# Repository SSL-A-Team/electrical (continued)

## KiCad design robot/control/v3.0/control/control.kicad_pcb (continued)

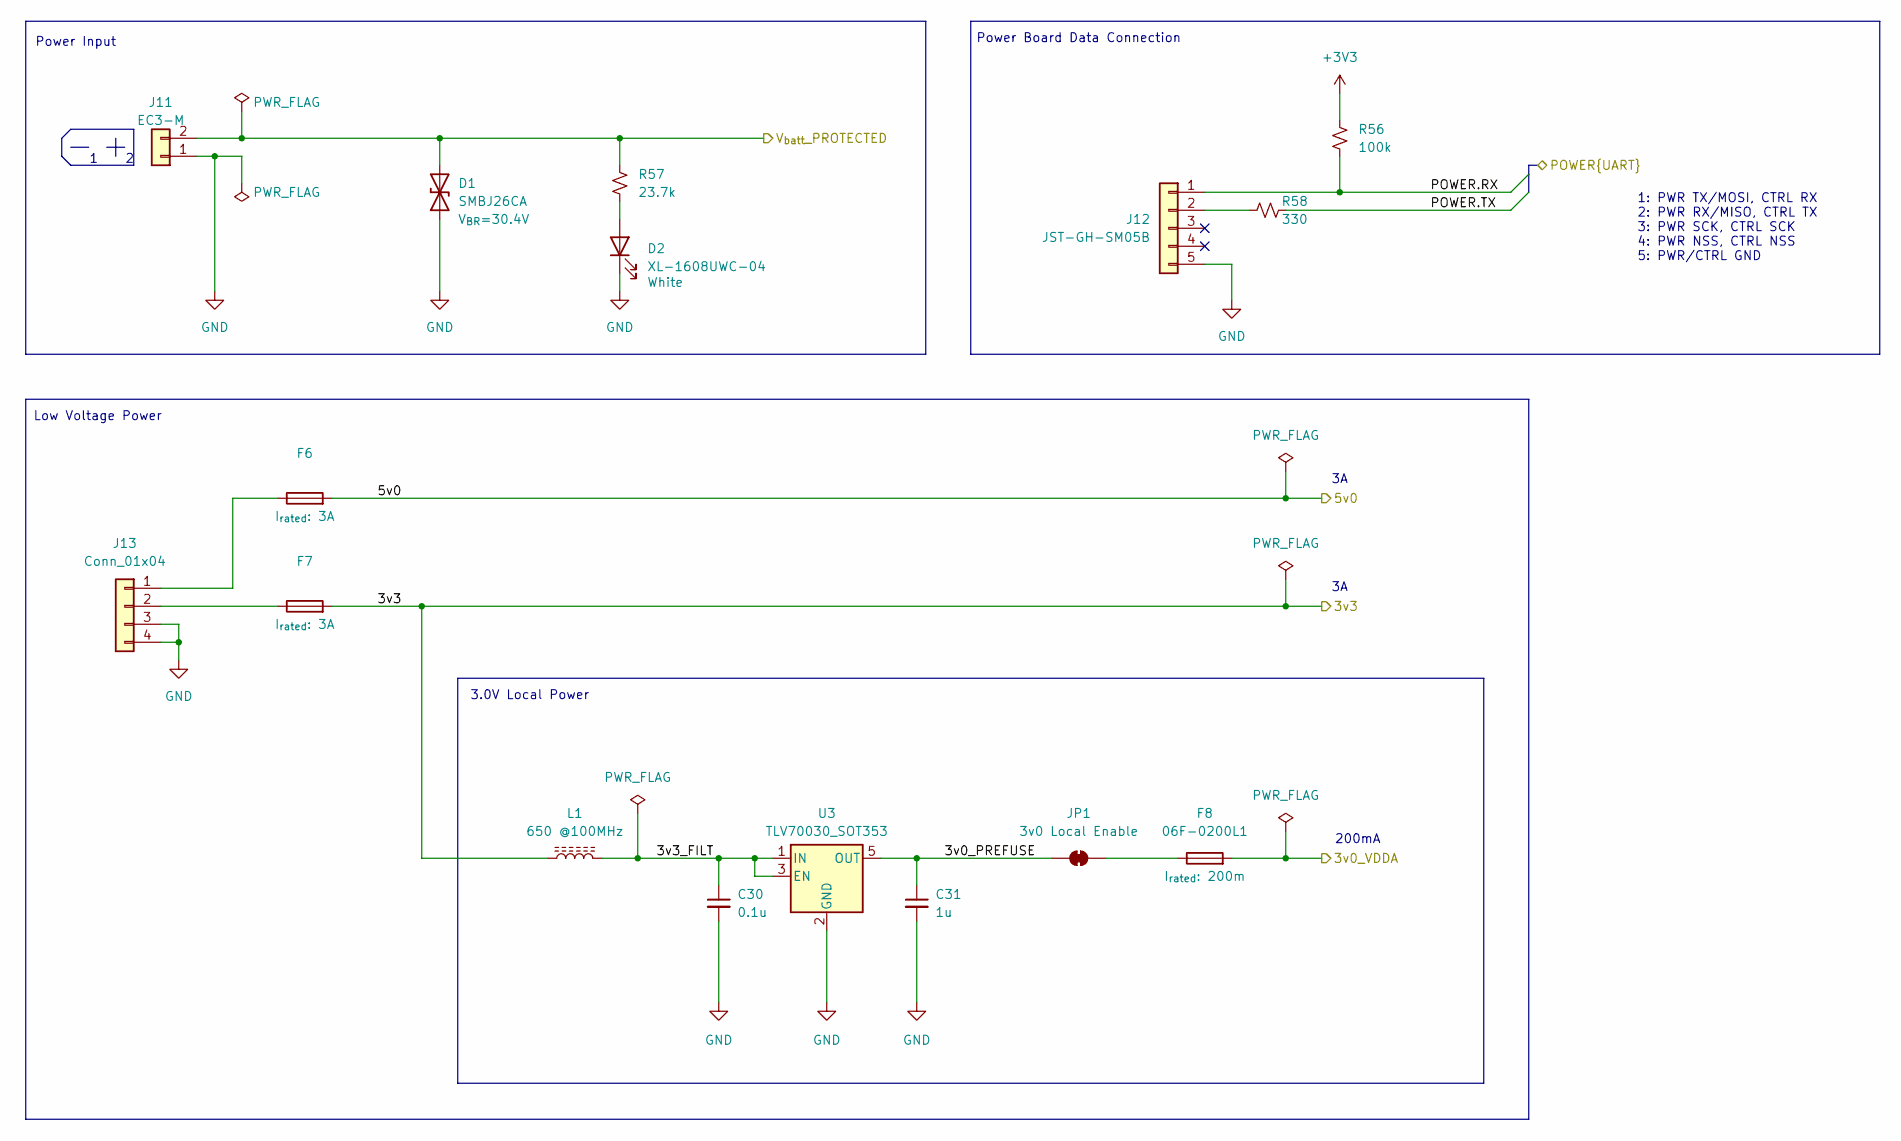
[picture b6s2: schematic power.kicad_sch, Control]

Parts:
C30: 0.1u; C_0402_1005Metric
C31: 1u; C_1206_3216Metric
D1: SMBJ26CA; D_SMB_Non-Polar
D2: XL-1608UWC-04; LED0603
F6, F7: Fuse_0603_1608Metric_Pad1.05x0.95mm_HandSolder
F8: 06F-0200L1; Fuse_0603_1608Metric_Pad1.05x0.95mm_HandSolder
J11: EC3-M; AMASS_XT30U-M_1x02_P5.0mm_Vertical
J12: JST-GH-SM05B; JST_GH_SM05B-GHS-TB_1x05-1MP_P1.25mm_Horizontal
J13: Conn_01x04; JST_PA_SM04B-PASS_1x04_P2.00mm_Horizontal
JP1: 3v0 Local Enable; SolderJumper-2_2.0x1.2mm_Closed
L1: 650 @100MHz; R_0603_1608Metric
R56: 100k; R_0402_1005Metric
R57: 23.7k; R_0402_1005Metric
R58: 330; R_0402_1005Metric
U3: TLV70030_SOT353; SOT-353_SC-70-5

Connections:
+3V0: F8.2; also elsewhere on the board
+3V3: F7.2, L1.1, R56.1; also elsewhere on the board
+5V: F6.2; also elsewhere on the board
+BATT: D1.2 (A2), J11.2, R57.1; also elsewhere on the board
/mcu/POWER.RX: J12.1, R56.2; also elsewhere on the board
/mcu/POWER.TX: R58.2; also elsewhere on the board
/power/3v0_PREFUSE: C31.1, JP1.1 (A), U3.5 (OUT)
/power/3v3_FILT: C30.1, L1.2, U3.1 (IN), U3.3 (EN)
GND: C30.2, C31.2, D1.1 (A1), D2.1 (K), J11.1, J12.5, J13.3, J13.4, U3.2 (GND); also elsewhere on the board
unnamed: D2.2 (A), R57.2
unnamed: J12.2, R58.1
unnamed: F6.1, J13.1
unnamed: F7.1, J13.2
unnamed: F8.1, JP1.2 (B)

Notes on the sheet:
200mA
Power Board Data Connection
1: PWR TX/MOSI, CTRL RX 2: PWR RX/MISO, CTRL TX 3: PWR SCK, CTRL SCK 4: PWR NSS, CTRL NSS 5: PWR/CTRL GND
Low Voltage Power
Power Input
3.0V Local Power

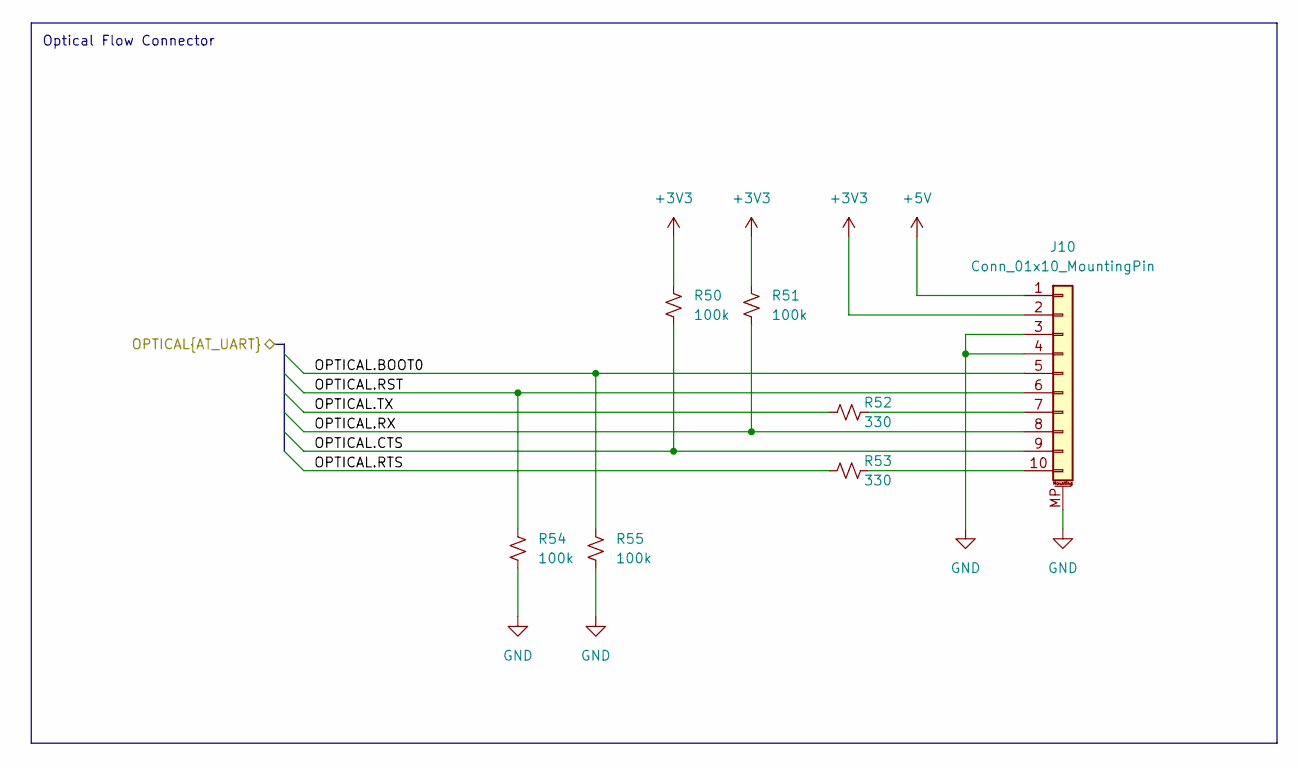
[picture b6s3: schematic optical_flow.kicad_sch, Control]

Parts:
J10: Conn_01x10_MountingPin; JST_GH_SM10B-GHS-TB_1x10-1MP_P1.25mm_Horizontal
R50, R51, R54, R55: 100k; R_0402_1005Metric
R52, R53: 330; R_0402_1005Metric

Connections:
+3V3: J10.2, R50.1, R51.1; also elsewhere on the board
+5V: J10.1; also elsewhere on the board
/mcu/OPTICAL_FLOW.BOOT0: J10.5, R55.1; also elsewhere on the board
/mcu/OPTICAL_FLOW.CTS: J10.9, R50.2; also elsewhere on the board
/mcu/OPTICAL_FLOW.RST: J10.6, R54.1; also elsewhere on the board
/mcu/OPTICAL_FLOW.RTS: R53.1; also elsewhere on the board
/mcu/OPTICAL_FLOW.RX: J10.8, R51.2; also elsewhere on the board
/mcu/OPTICAL_FLOW.TX: R52.1; also elsewhere on the board
GND: J10.3, J10.4, J10.MP (MountPin), R54.2, R55.2; also elsewhere on the board
unnamed: J10.7, R52.2
unnamed: J10.10, R53.2

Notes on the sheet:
Optical Flow Connector

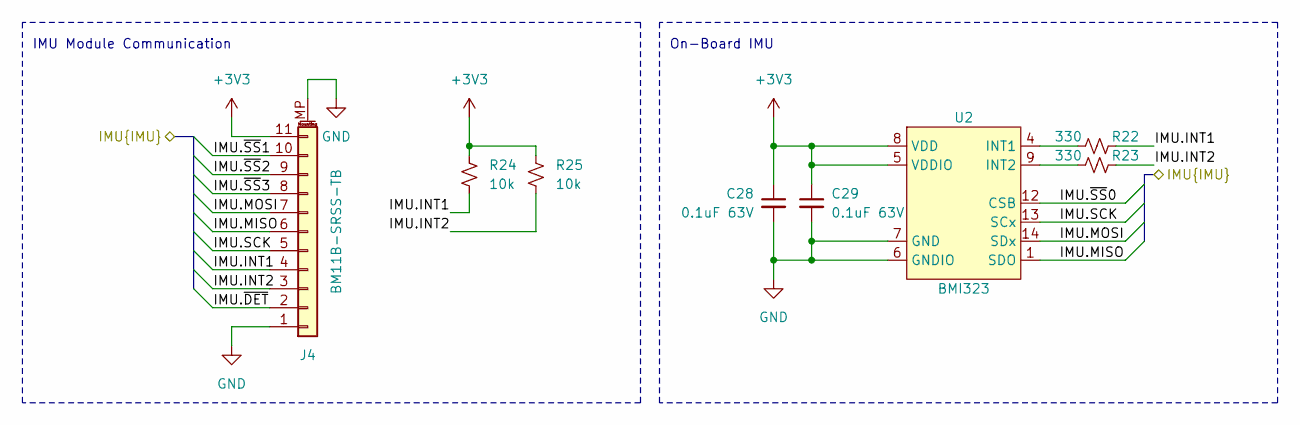
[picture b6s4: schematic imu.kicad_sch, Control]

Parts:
C28, C29: 0.1uF 63V; C_0402_1005Metric
J4: BM11B-SRSS-TB; JST_SH_BM11B-SRSS-TB_1x11-1MP_P1.00mm_Vertical
R22, R23: 330; R_0402_1005Metric
R24, R25: 10k; R_0402_1005Metric
U2: BMI323

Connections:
+3V3: C28.1, C29.1, J4.11, R24.1, R25.1, U2.5 (VDDIO), U2.8 (VDD); also elsewhere on the board
/imu/IMU.INT1: J4.4, R22.2, R24.2; also elsewhere on the board
/imu/IMU.INT2: J4.3, R23.2, R25.2; also elsewhere on the board
/imu/IMU.MISO: J4.6, U2.1 (SDO); also elsewhere on the board
/imu/IMU.MOSI: J4.7, U2.14 (SDx); also elsewhere on the board
/imu/IMU.SCK: J4.5, U2.13 (SCx); also elsewhere on the board
/imu/IMU.~DET: J4.2; also elsewhere on the board
/imu/IMU.~SS0: U2.12 (CSB); also elsewhere on the board
/imu/IMU.~SS1: J4.10; also elsewhere on the board
/imu/IMU.~SS2: J4.9; also elsewhere on the board
/imu/IMU.~SS3: J4.8; also elsewhere on the board
GND: C28.2, C29.2, J4.1, J4.MP (MountPin), U2.6 (GNDIO), U2.7 (GND); also elsewhere on the board
unnamed: R22.1, U2.4 (INT1)
unnamed: R23.1, U2.9 (INT2)

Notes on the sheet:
On-Board IMU
IMU Module Communication

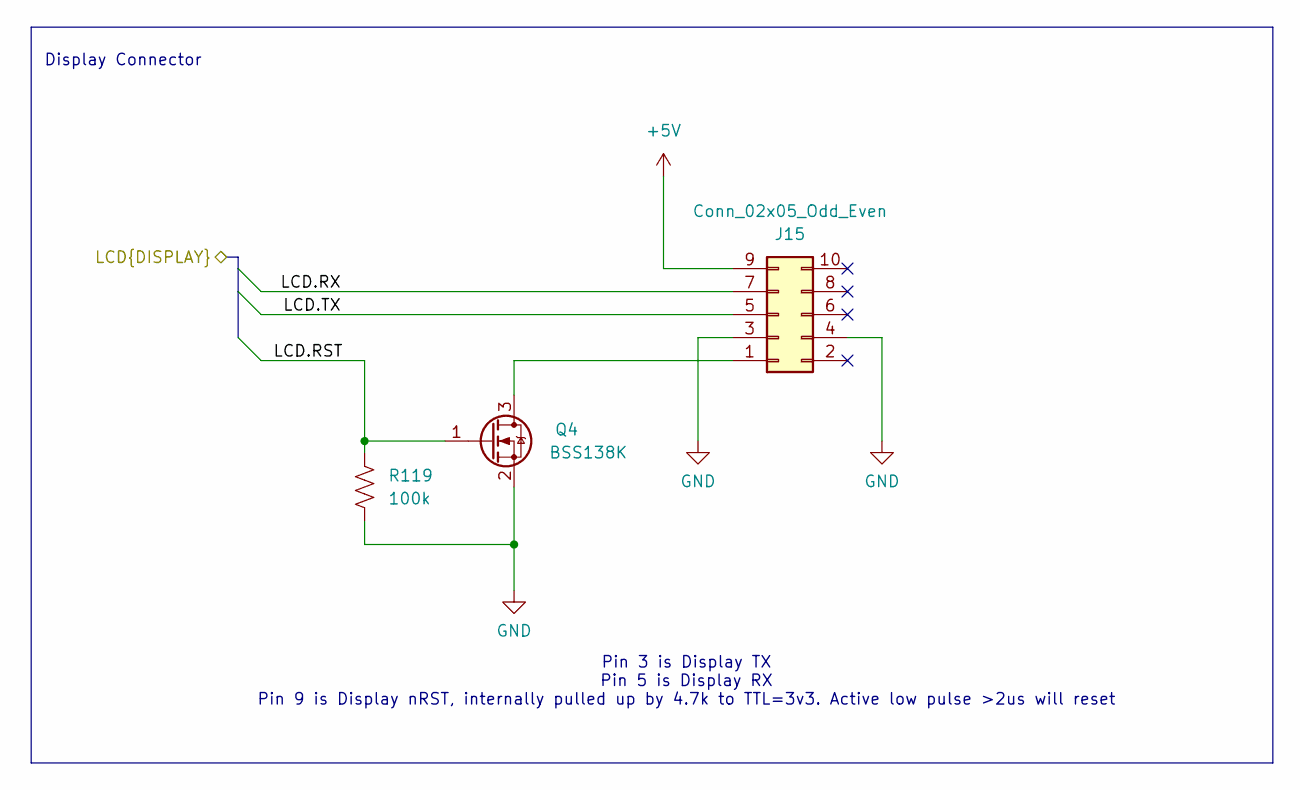
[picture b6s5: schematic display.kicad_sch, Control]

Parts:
J15: Conn_02x05_Odd_Even; PinHeader_2x05_P2.54mm_Vertical
Q4: BSS138K; SOT-23
R119: 100k; R_0402_1005Metric

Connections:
+5V: J15.9; also elsewhere on the board
/display/LCD.RST: Q4.1 (G), R119.1; also elsewhere on the board
/display/LCD.RX: J15.7; also elsewhere on the board
/display/LCD.TX: J15.5; also elsewhere on the board
GND: J15.3, J15.4, Q4.2 (S), R119.2; also elsewhere on the board
unnamed: J15.1, Q4.3 (D)

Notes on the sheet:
Pin 3 is Display TX Pin 5 is Display RX Pin 9 is Display nRST, internally pulled up by 4.7k to TTL=3v3. Active low pulse >2us will reset
Display Connector

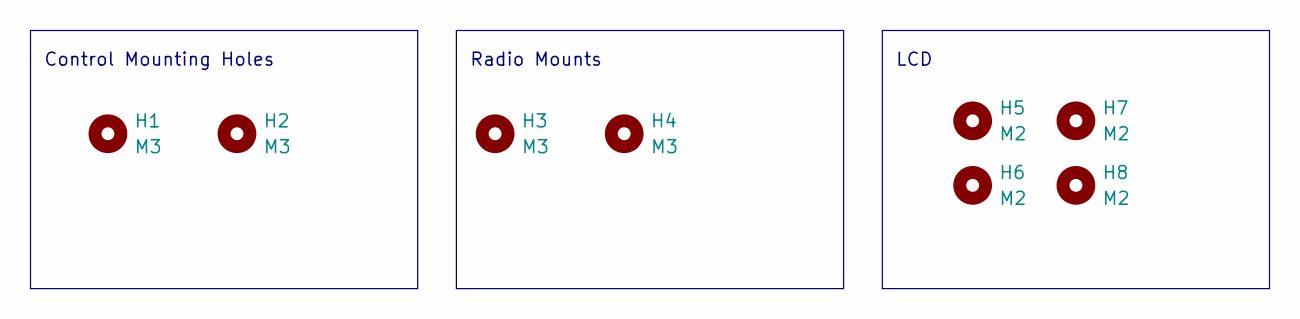
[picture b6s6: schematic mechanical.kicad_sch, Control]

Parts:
H1, H2, H3, H4: M3; MountingHole_3.2mm_M3_Pad_TopBottom
H5, H6, H7, H8: M2; MountingHole_2.2mm_M2_DIN965_Pad

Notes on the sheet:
LCD
Radio Mounts
Control Mounting Holes

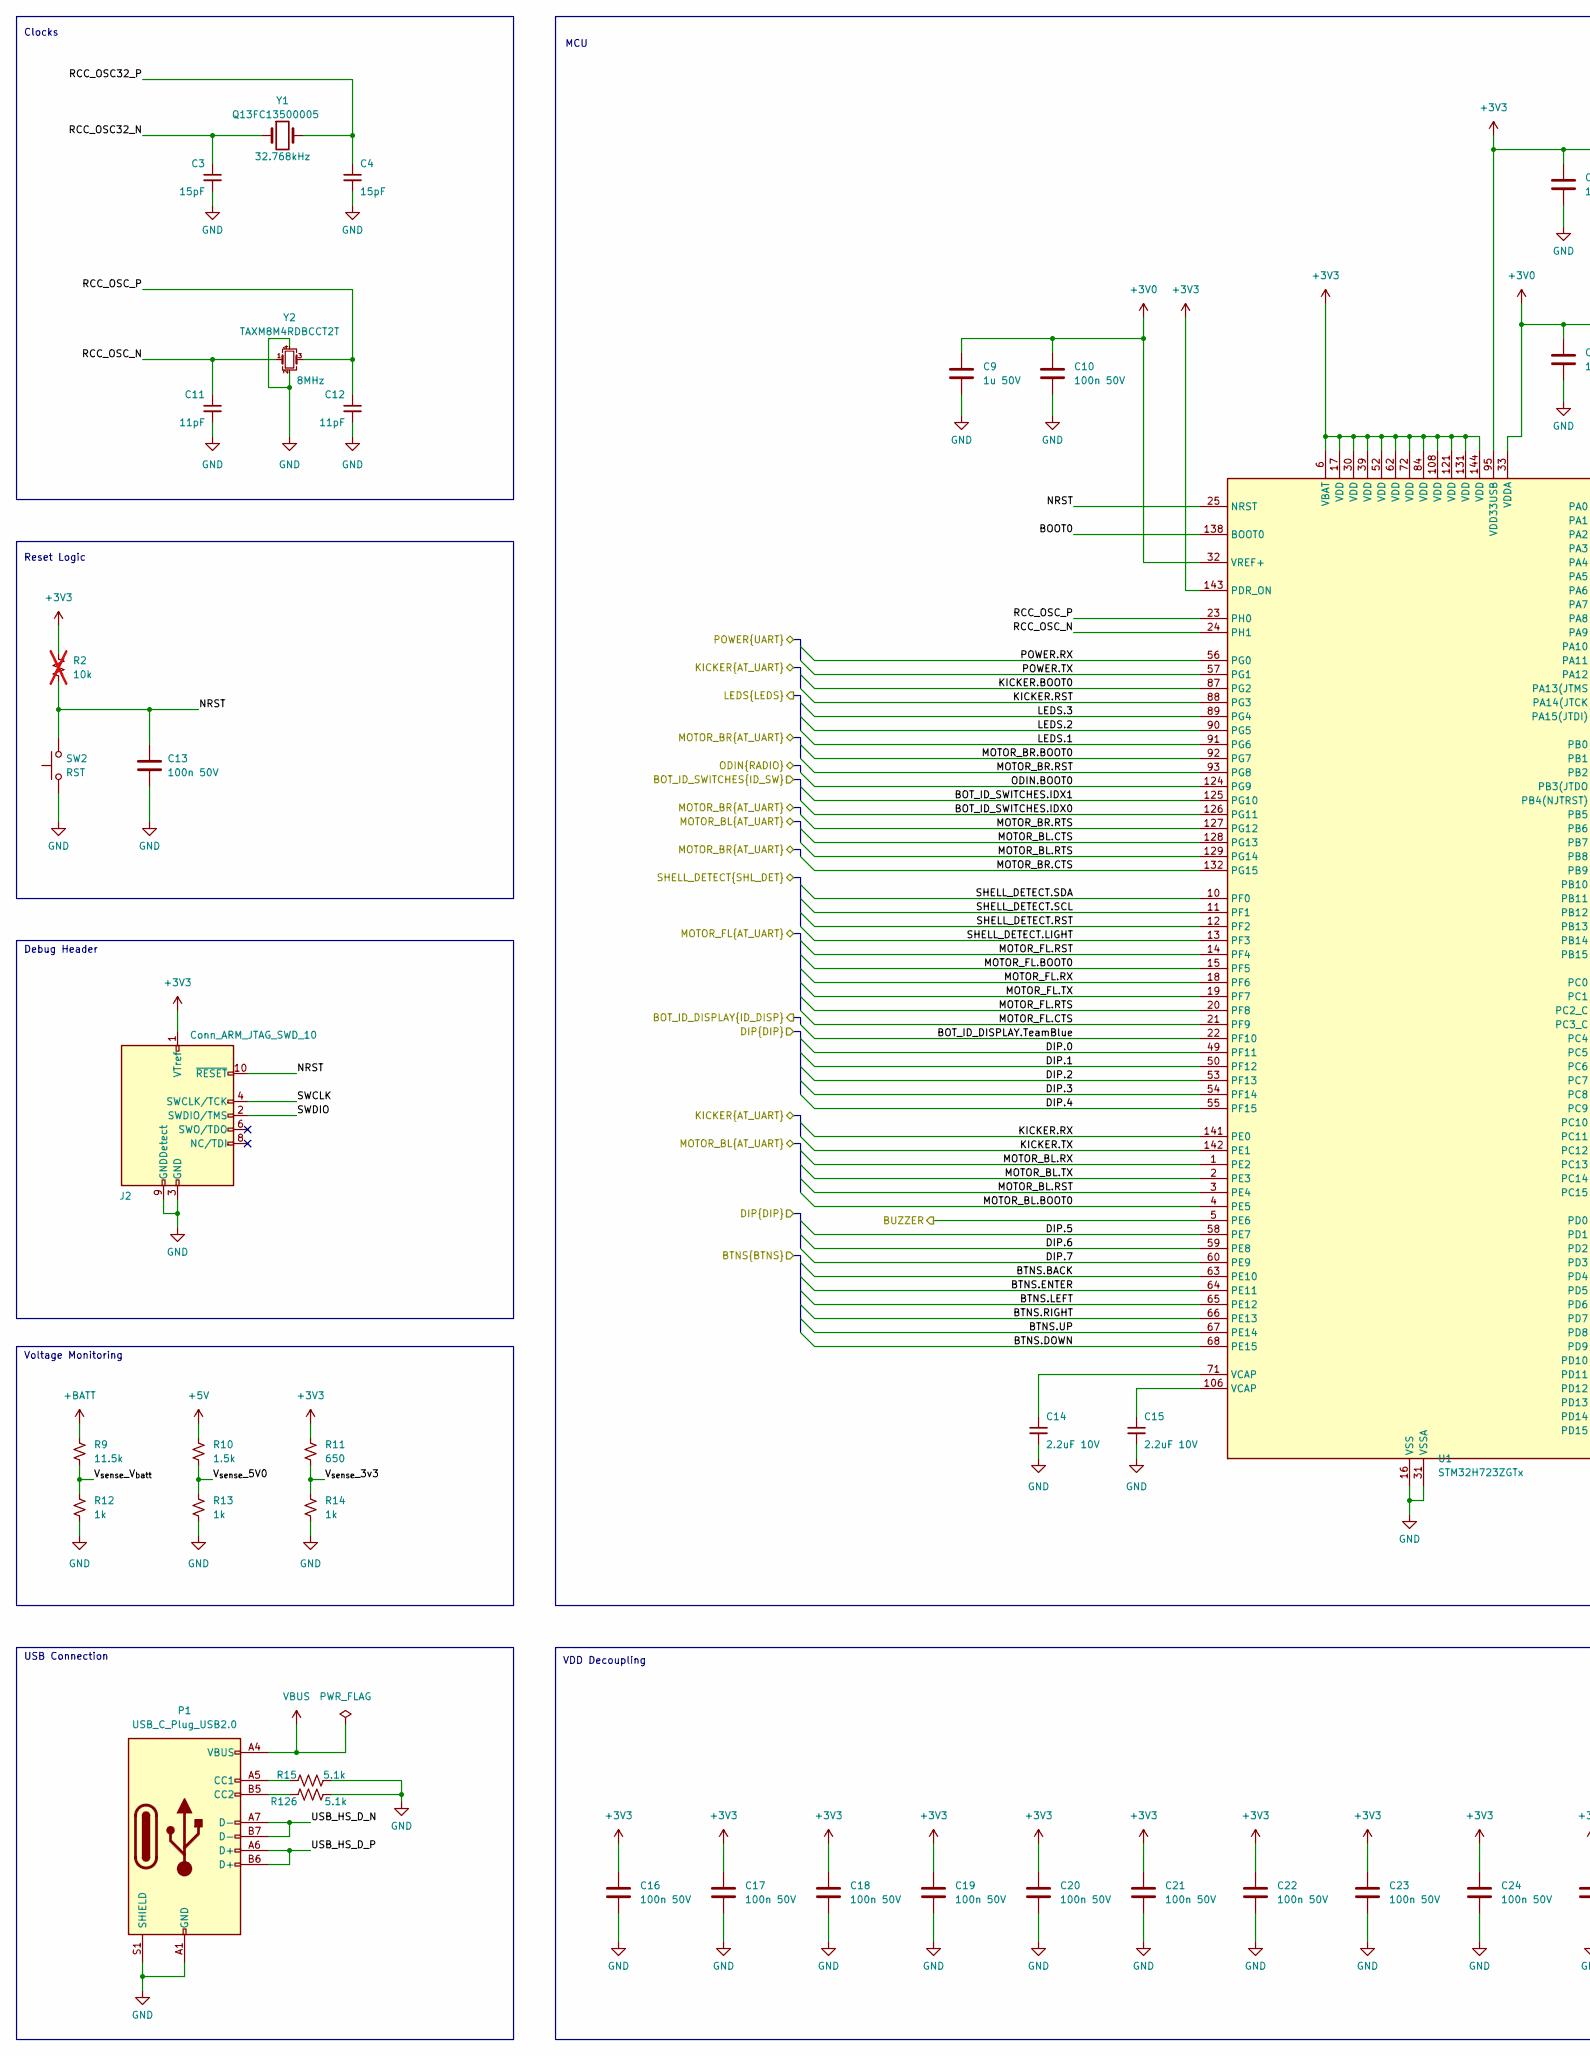
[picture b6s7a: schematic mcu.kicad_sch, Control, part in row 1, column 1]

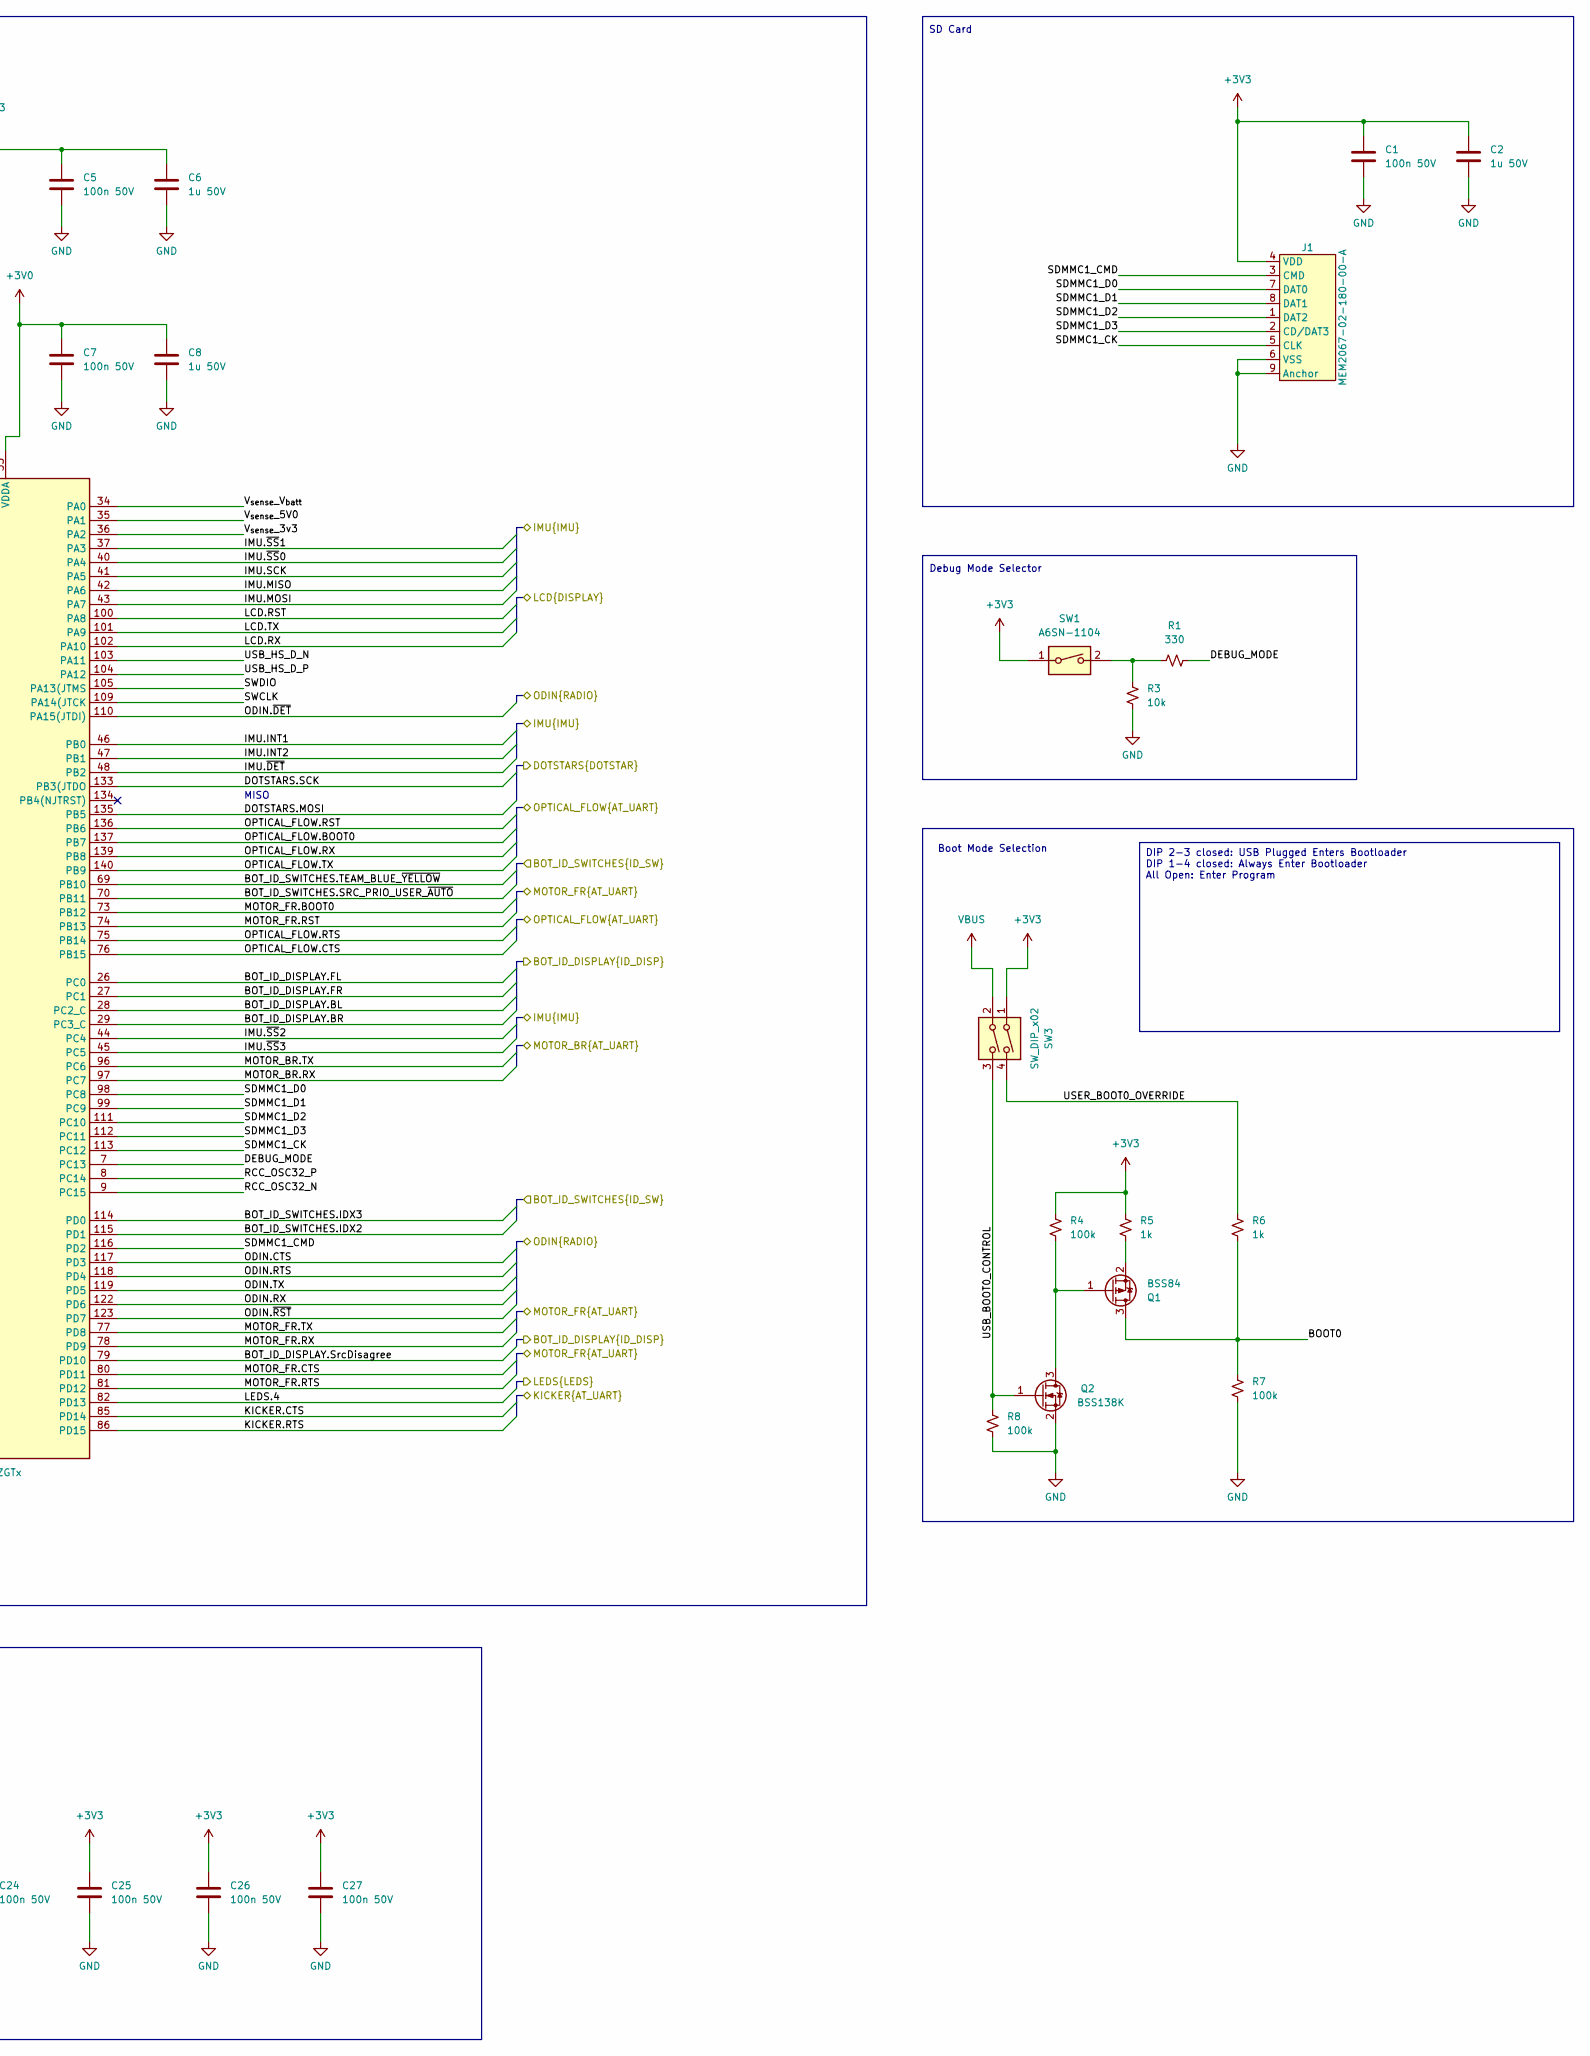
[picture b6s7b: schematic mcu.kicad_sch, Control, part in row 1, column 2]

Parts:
C1, C5, C7, C10, C13, C16, C17, C18, C19, C20, C21, C22, C23, C24, C25, C26, C27: 100n 50V; C_0402_1005Metric
C2, C6, C8, C9: 1u 50V; C_0402_1005Metric
C3, C4: 15pF; C_0402_1005Metric
C11, C12: 11pF; C_0402_1005Metric
C14, C15: 2.2uF 10V; C_0603_1608Metric
J1: MEM2067-02-180-00-A
J2: Conn_ARM_JTAG_SWD_10; Samtec-2x5pin-1.27mm
P1: USB_C_Plug_USB2.0; USB_C_Receptacle_Molex_105450-0101
Q1: BSS84; SOT-23
Q2: BSS138K; SOT-23
R1: 330; R_0402_1005Metric
R2: 10k; R_0402_1005Metric; not fitted
R3: 10k; R_0402_1005Metric
R4, R7, R8: 100k; R_0402_1005Metric
R5, R6, R12, R13, R14: 1k; R_0402_1005Metric
R9: 11.5k; R_0402_1005Metric
R10: 1.5k; R_0402_1005Metric
R11: 650; R_0402_1005Metric
R15, R126: 5.1k; R_0402_1005Metric
SW1: A6SN-1104; SW_DIP_SPSTx01_Slide_Omron_A6S-110x_W8.9mm_P2.54mm
SW2: RST; SW_SPST_TL3305A
SW3: SW_DIP_x02; 219-2MST
U1: STM32H723ZGTx; LQFP-144_20x20mm_P0.5mm
Y1: Q13FC13500005; Crystal_SMD_3215-2Pin_3.2x1.5mm
Y2: TAXM8M4RDBCCT2T; Crystal_SMD_3225-4Pin_3.2x2.5mm

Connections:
+3V0: C7.1, C8.1, C9.1, C10.1, U1.32 (VREF+), U1.33 (VDDA); also elsewhere on the board
+3V3: C1.1, C2.1, C5.1, C6.1, C16.1, C17.1, C18.1, C19.1, C20.1, C21.1, C22.1, C23.1, C24.1, C25.1, C26.1, C27.1, J1.4 (VDD), J2.1 (VTref), R2.1, R4.1, R5.1, R11.1, SW1.1, SW3.1, U1.6 (VBAT), U1.17 (VDD), U1.30 (VDD), U1.39 (VDD), U1.52 (VDD), U1.62 (VDD), U1.72 (VDD), U1.84 (VDD), U1.95 (VDD33USB), U1.108 (VDD), U1.121 (VDD), U1.131 (VDD), U1.143 (PDR_ON), U1.144 (VDD); also elsewhere on the board
+5V: R10.1; also elsewhere on the board
+BATT: R9.1; also elsewhere on the board
/back_left_drive_motor/MOTOR.BOOT0: U1.4 (PE5); also elsewhere on the board
/back_left_drive_motor/MOTOR.CTS: U1.128 (PG13); also elsewhere on the board
/back_left_drive_motor/MOTOR.RST: U1.3 (PE4); also elsewhere on the board
/back_left_drive_motor/MOTOR.RTS: U1.129 (PG14); also elsewhere on the board
/back_left_drive_motor/MOTOR.RX: U1.1 (PE2); also elsewhere on the board
/back_left_drive_motor/MOTOR.TX: U1.2 (PE3); also elsewhere on the board
/back_right_drive_motor/MOTOR.BOOT0: U1.92 (PG7); also elsewhere on the board
/back_right_drive_motor/MOTOR.CTS: U1.132 (PG15); also elsewhere on the board
/back_right_drive_motor/MOTOR.RST: U1.93 (PG8); also elsewhere on the board
/back_right_drive_motor/MOTOR.RTS: U1.127 (PG12); also elsewhere on the board
/back_right_drive_motor/MOTOR.RX: U1.97 (PC7); also elsewhere on the board
/back_right_drive_motor/MOTOR.TX: U1.96 (PC6); also elsewhere on the board
/display/LCD.RST: U1.100 (PA8); also elsewhere on the board
/display/LCD.RX: U1.102 (PA10); also elsewhere on the board
/display/LCD.TX: U1.101 (PA9); also elsewhere on the board
/front_left_drive_motor/MOTOR.BOOT0: U1.15 (PF5); also elsewhere on the board
/front_left_drive_motor/MOTOR.CTS: U1.21 (PF9); also elsewhere on the board
/front_left_drive_motor/MOTOR.RST: U1.14 (PF4); also elsewhere on the board
/front_left_drive_motor/MOTOR.RTS: U1.20 (PF8); also elsewhere on the board
/front_left_drive_motor/MOTOR.RX: U1.18 (PF6); also elsewhere on the board
/front_left_drive_motor/MOTOR.TX: U1.19 (PF7); also elsewhere on the board
/front_right_drive_motor/MOTOR.BOOT0: U1.73 (PB12); also elsewhere on the board
/front_right_drive_motor/MOTOR.CTS: U1.80 (PD11); also elsewhere on the board
/front_right_drive_motor/MOTOR.RST: U1.74 (PB13); also elsewhere on the board
/front_right_drive_motor/MOTOR.RTS: U1.81 (PD12); also elsewhere on the board
/front_right_drive_motor/MOTOR.RX: U1.78 (PD9); also elsewhere on the board
/front_right_drive_motor/MOTOR.TX: U1.77 (PD8); also elsewhere on the board
/imu/IMU.INT1: U1.46 (PB0); also elsewhere on the board
/imu/IMU.INT2: U1.47 (PB1); also elsewhere on the board
/imu/IMU.MISO: U1.42 (PA6); also elsewhere on the board
/imu/IMU.MOSI: U1.43 (PA7); also elsewhere on the board
/imu/IMU.SCK: U1.41 (PA5); also elsewhere on the board
/imu/IMU.~DET: U1.48 (PB2); also elsewhere on the board
/imu/IMU.~SS0: U1.40 (PA4); also elsewhere on the board
/imu/IMU.~SS1: U1.37 (PA3); also elsewhere on the board
/imu/IMU.~SS2: U1.44 (PC4); also elsewhere on the board
/imu/IMU.~SS3: U1.45 (PC5); also elsewhere on the board
/kicker/KICKER.BOOT0: U1.87 (PG2); also elsewhere on the board
/kicker/KICKER.CTS: U1.85 (PD14); also elsewhere on the board
/kicker/KICKER.RST: U1.88 (PG3); also elsewhere on the board
/kicker/KICKER.RTS: U1.86 (PD15); also elsewhere on the board
/kicker/KICKER.RX: U1.141 (PE0); also elsewhere on the board
/kicker/KICKER.TX: U1.142 (PE1); also elsewhere on the board
/mcu/BOOT0: Q1.3 (D), R6.2, R7.1, U1.138 (BOOT0)
/mcu/BOT_ID_DISPLAY.BL: U1.28 (PC2_C); also elsewhere on the board
/mcu/BOT_ID_DISPLAY.BR: U1.29 (PC3_C); also elsewhere on the board
/mcu/BOT_ID_DISPLAY.FL: U1.26 (PC0); also elsewhere on the board
/mcu/BOT_ID_DISPLAY.FR: U1.27 (PC1); also elsewhere on the board
/mcu/BOT_ID_DISPLAY.SrcDisagree: U1.79 (PD10); also elsewhere on the board
/mcu/BOT_ID_DISPLAY.TeamBlue: U1.22 (PF10); also elsewhere on the board
/mcu/BOT_ID_SWITCHES.IDX0: U1.126 (PG11); also elsewhere on the board
/mcu/BOT_ID_SWITCHES.IDX1: U1.125 (PG10); also elsewhere on the board
/mcu/BOT_ID_SWITCHES.IDX2: U1.115 (PD1); also elsewhere on the board
/mcu/BOT_ID_SWITCHES.IDX3: U1.114 (PD0); also elsewhere on the board
/mcu/BOT_ID_SWITCHES.SRC_PRIO_USER_~AUTO: U1.70 (PB11); also elsewhere on the board
/mcu/BOT_ID_SWITCHES.TEAM_BLUE_~YELLOW: U1.69 (PB10); also elsewhere on the board
/mcu/BTNS.BACK: U1.63 (PE10); also elsewhere on the board
/mcu/BTNS.DOWN: U1.68 (PE15); also elsewhere on the board
/mcu/BTNS.ENTER: U1.64 (PE11); also elsewhere on the board
/mcu/BTNS.LEFT: U1.65 (PE12); also elsewhere on the board
/mcu/BTNS.RIGHT: U1.66 (PE13); also elsewhere on the board
/mcu/BTNS.UP: U1.67 (PE14); also elsewhere on the board
/mcu/BUZZER: U1.5 (PE6); also elsewhere on the board
/mcu/DEBUG_MODE: R1.2, U1.7 (PC13)
/mcu/DIP.0: U1.49 (PF11); also elsewhere on the board
/mcu/DIP.1: U1.50 (PF12); also elsewhere on the board
/mcu/DIP.2: U1.53 (PF13); also elsewhere on the board
/mcu/DIP.3: U1.54 (PF14); also elsewhere on the board
/mcu/DIP.4: U1.55 (PF15); also elsewhere on the board
/mcu/DIP.5: U1.58 (PE7); also elsewhere on the board
/mcu/DIP.6: U1.59 (PE8); also elsewhere on the board
/mcu/DIP.7: U1.60 (PE9); also elsewhere on the board
/mcu/DOTSTARS.MOSI: U1.135 (PB5); also elsewhere on the board
/mcu/DOTSTARS.SCK: U1.133 (PB3(JTDO); also elsewhere on the board
/mcu/LEDS.1: U1.91 (PG6); also elsewhere on the board
/mcu/LEDS.2: U1.90 (PG5); also elsewhere on the board
/mcu/LEDS.3: U1.89 (PG4); also elsewhere on the board
/mcu/LEDS.4: U1.82 (PD13); also elsewhere on the board
/mcu/NRST: C13.1, J2.10 (~RESET), R2.2, SW2.2, U1.25 (NRST)
/mcu/ODIN.BOOT0: U1.124 (PG9); also elsewhere on the board
/mcu/ODIN.CTS: U1.117 (PD3); also elsewhere on the board
/mcu/ODIN.RTS: U1.118 (PD4); also elsewhere on the board
/mcu/ODIN.RX: U1.122 (PD6); also elsewhere on the board
/mcu/ODIN.TX: U1.119 (PD5); also elsewhere on the board
/mcu/ODIN.~DET: U1.110 (PA15(JTDI)); also elsewhere on the board
/mcu/ODIN.~RST: U1.123 (PD7); also elsewhere on the board
/mcu/OPTICAL_FLOW.BOOT0: U1.137 (PB7); also elsewhere on the board
/mcu/OPTICAL_FLOW.CTS: U1.76 (PB15); also elsewhere on the board
/mcu/OPTICAL_FLOW.RST: U1.136 (PB6); also elsewhere on the board
/mcu/OPTICAL_FLOW.RTS: U1.75 (PB14); also elsewhere on the board
/mcu/OPTICAL_FLOW.RX: U1.139 (PB8); also elsewhere on the board
/mcu/OPTICAL_FLOW.TX: U1.140 (PB9); also elsewhere on the board
/mcu/POWER.RX: U1.56 (PG0); also elsewhere on the board
/mcu/POWER.TX: U1.57 (PG1); also elsewhere on the board
/mcu/RCC_OSC32_N: C3.1, U1.9 (PC15), Y1.1
/mcu/RCC_OSC32_P: C4.1, U1.8 (PC14), Y1.2
/mcu/RCC_OSC_N: C11.1, U1.24 (PH1), Y2.1
/mcu/RCC_OSC_P: C12.1, U1.23 (PH0), Y2.3
/mcu/SDMMC1_CK: J1.5 (CLK), U1.113 (PC12)
/mcu/SDMMC1_CMD: J1.3 (CMD), U1.116 (PD2)
/mcu/SDMMC1_D0: J1.7 (DAT0), U1.98 (PC8)
/mcu/SDMMC1_D1: J1.8 (DAT1), U1.99 (PC9)
/mcu/SDMMC1_D2: J1.1 (DAT2), U1.111 (PC10)
/mcu/SDMMC1_D3: J1.2 (CD/DAT3), U1.112 (PC11)
/mcu/SHELL_DETECT.LIGHT: U1.13 (PF3); also elsewhere on the board
/mcu/SHELL_DETECT.RST: U1.12 (PF2); also elsewhere on the board
/mcu/SHELL_DETECT.SCL: U1.11 (PF1); also elsewhere on the board
/mcu/SHELL_DETECT.SDA: U1.10 (PF0); also elsewhere on the board
/mcu/SWCLK: J2.4 (SWCLK/TCK), U1.109 (PA14(JTCK)
/mcu/SWDIO: J2.2 (SWDIO/TMS), U1.105 (PA13(JTMS)
/mcu/USB_BOOT0_CONTROL: Q2.1 (G), R8.1, SW3.3
/mcu/USB_HS_D_N: P1.A7 (D-), P1.B7 (D-), U1.103 (PA11)
/mcu/USB_HS_D_P: P1.A6 (D+), P1.B6 (D+), U1.104 (PA12)
/mcu/USER_BOOT0_OVERRIDE: R6.1, SW3.4
/mcu/V_{sense}_3v3: R11.2, R14.1, U1.36 (PA2)
/mcu/V_{sense}_5V0: R10.2, R13.1, U1.35 (PA1)
/mcu/V_{sense}_V_{batt}: R9.2, R12.1, U1.34 (PA0)
GND: C1.2, C2.2, C3.2, C4.2, C5.2, C6.2, C7.2, C8.2, C9.2, C10.2, C11.2, C12.2, C13.2, C14.2, C15.2, C16.2, C17.2, C18.2, C19.2, C20.2, C21.2, C22.2, C23.2, C24.2, C25.2, C26.2, C27.2, J1.6 (VSS), J1.9 (Anchor), J2.3 (GND), J2.5 (GND), J2.9 (GNDDetect), P1.A1 (GND), P1.A12 (GND), P1.B1 (GND), P1.B12 (GND), P1.S1 (SHIELD), Q2.2 (S), R3.2, R7.2, R8.2, R12.2, R13.2, R14.2, R15.2, R126.2, SW2.1, U1.16 (VSS), U1.31 (VSSA), U1.38 (VSS), U1.51 (VSS), U1.61 (VSS), U1.83 (VSS), U1.94 (VSS), U1.107 (VSS), U1.120 (VSS), U1.130 (VSS), Y2.2, Y2.4; also elsewhere on the board
unnamed: C14.1, U1.71 (VCAP)
unnamed: C15.1, U1.106 (VCAP)
unnamed: P1.A5 (CC1), R15.1
unnamed: P1.B5 (CC2), R126.1
unnamed: Q1.1 (G), Q2.3 (D), R4.2
unnamed: Q1.2 (S), R5.2
unnamed: R1.1, R3.1, SW1.2
VBUS: P1.A4 (VBUS), P1.A9 (VBUS), P1.B4 (VBUS), P1.B9 (VBUS), SW3.2

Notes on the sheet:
DIP 2-3 closed: USB Plugged Enters Bootloader DIP 1-4 closed: Always Enter Bootloader All Open: Enter Program
USB Connection
MCU
Clocks
Debug Header
VDD Decoupling
Debug Mode Selector
Voltage Monitoring
Reset Logic
SD Card
MISO
Boot Mode Selection

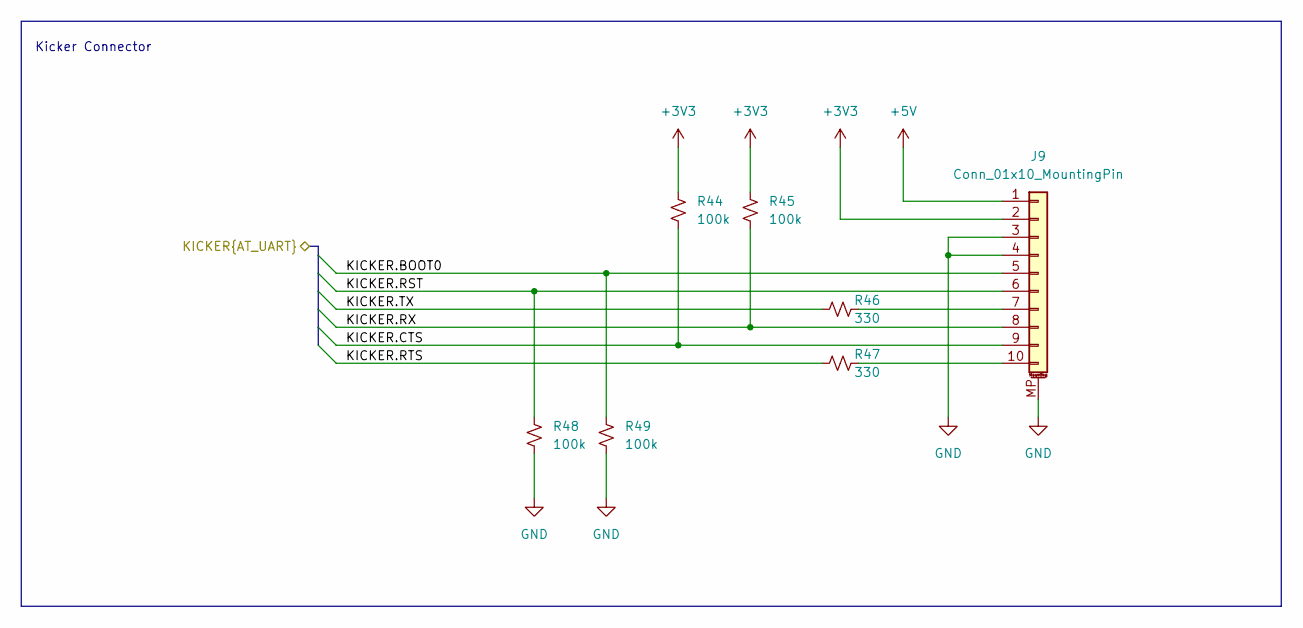
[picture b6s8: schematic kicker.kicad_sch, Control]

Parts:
J9: Conn_01x10_MountingPin; JST_GH_SM10B-GHS-TB_1x10-1MP_P1.25mm_Horizontal
R44, R45, R48, R49: 100k; R_0402_1005Metric
R46, R47: 330; R_0402_1005Metric

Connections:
+3V3: J9.2, R44.1, R45.1; also elsewhere on the board
+5V: J9.1; also elsewhere on the board
/kicker/KICKER.BOOT0: J9.5, R49.1; also elsewhere on the board
/kicker/KICKER.CTS: J9.9, R44.2; also elsewhere on the board
/kicker/KICKER.RST: J9.6, R48.1; also elsewhere on the board
/kicker/KICKER.RTS: R47.1; also elsewhere on the board
/kicker/KICKER.RX: J9.8, R45.2; also elsewhere on the board
/kicker/KICKER.TX: R46.1; also elsewhere on the board
GND: J9.3, J9.4, J9.MP (MountPin), R48.2, R49.2; also elsewhere on the board
unnamed: J9.7, R46.2
unnamed: J9.10, R47.2

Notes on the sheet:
Kicker Connector
